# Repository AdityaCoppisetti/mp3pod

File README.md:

for the longest time i wanted to build a mp3 player and 
so i decided to build one using hackclub's macondo program which will also provide me funds
to build it. 
i absolutely love e ink display and decided to use that as i was also using it for my kindle project.
this is how my build looks like 

im a sucker for single purpose devices. 
i used to own a mp3 player when i was a little kid and i used to take that little nugget along with me everywhere. 
but then i lost it which was very unfortunate. 
hackclub's macondo program honestly just gave me a reason to make one. 

and i decided to make it also because it would help me improve my schematic , pcb understanding/ making skills 

here are some questions you must be wondering 
1) did i use ai for this project?
   - yes i kind of did use ai. i used it to make sure my wiring was correct by providing chatgpt screenshots and asking for feedback.
2) is there bluetooth?
   - yes the esp32 module im using has inbuilt bluetooth so i can connect my bluetooth headphones.
3) does it have storage?
   - yes ive put a sd card module and i will insert a sd card into it with my songs already loaded.
4) does it have wifi?
   - ayes the esp 32 module im using also has wifi.
5) can you listen to songs that you havent downloaded?
   - yes using wifi , i can build a ui and load all my songs into my home server and listen to music while connected to wifi anywhere i am.
6) what would happen if i run out of storage
   - i can load the songs that i am not able to download onto my home server and listen to it when the device is online.
7) how do you load songs onto it
   - you can load the songs onto the sd card or you could upload it onto the sd card via bluetooth or wifi using the esp32 module. 

ive gotten really good at building pcbs

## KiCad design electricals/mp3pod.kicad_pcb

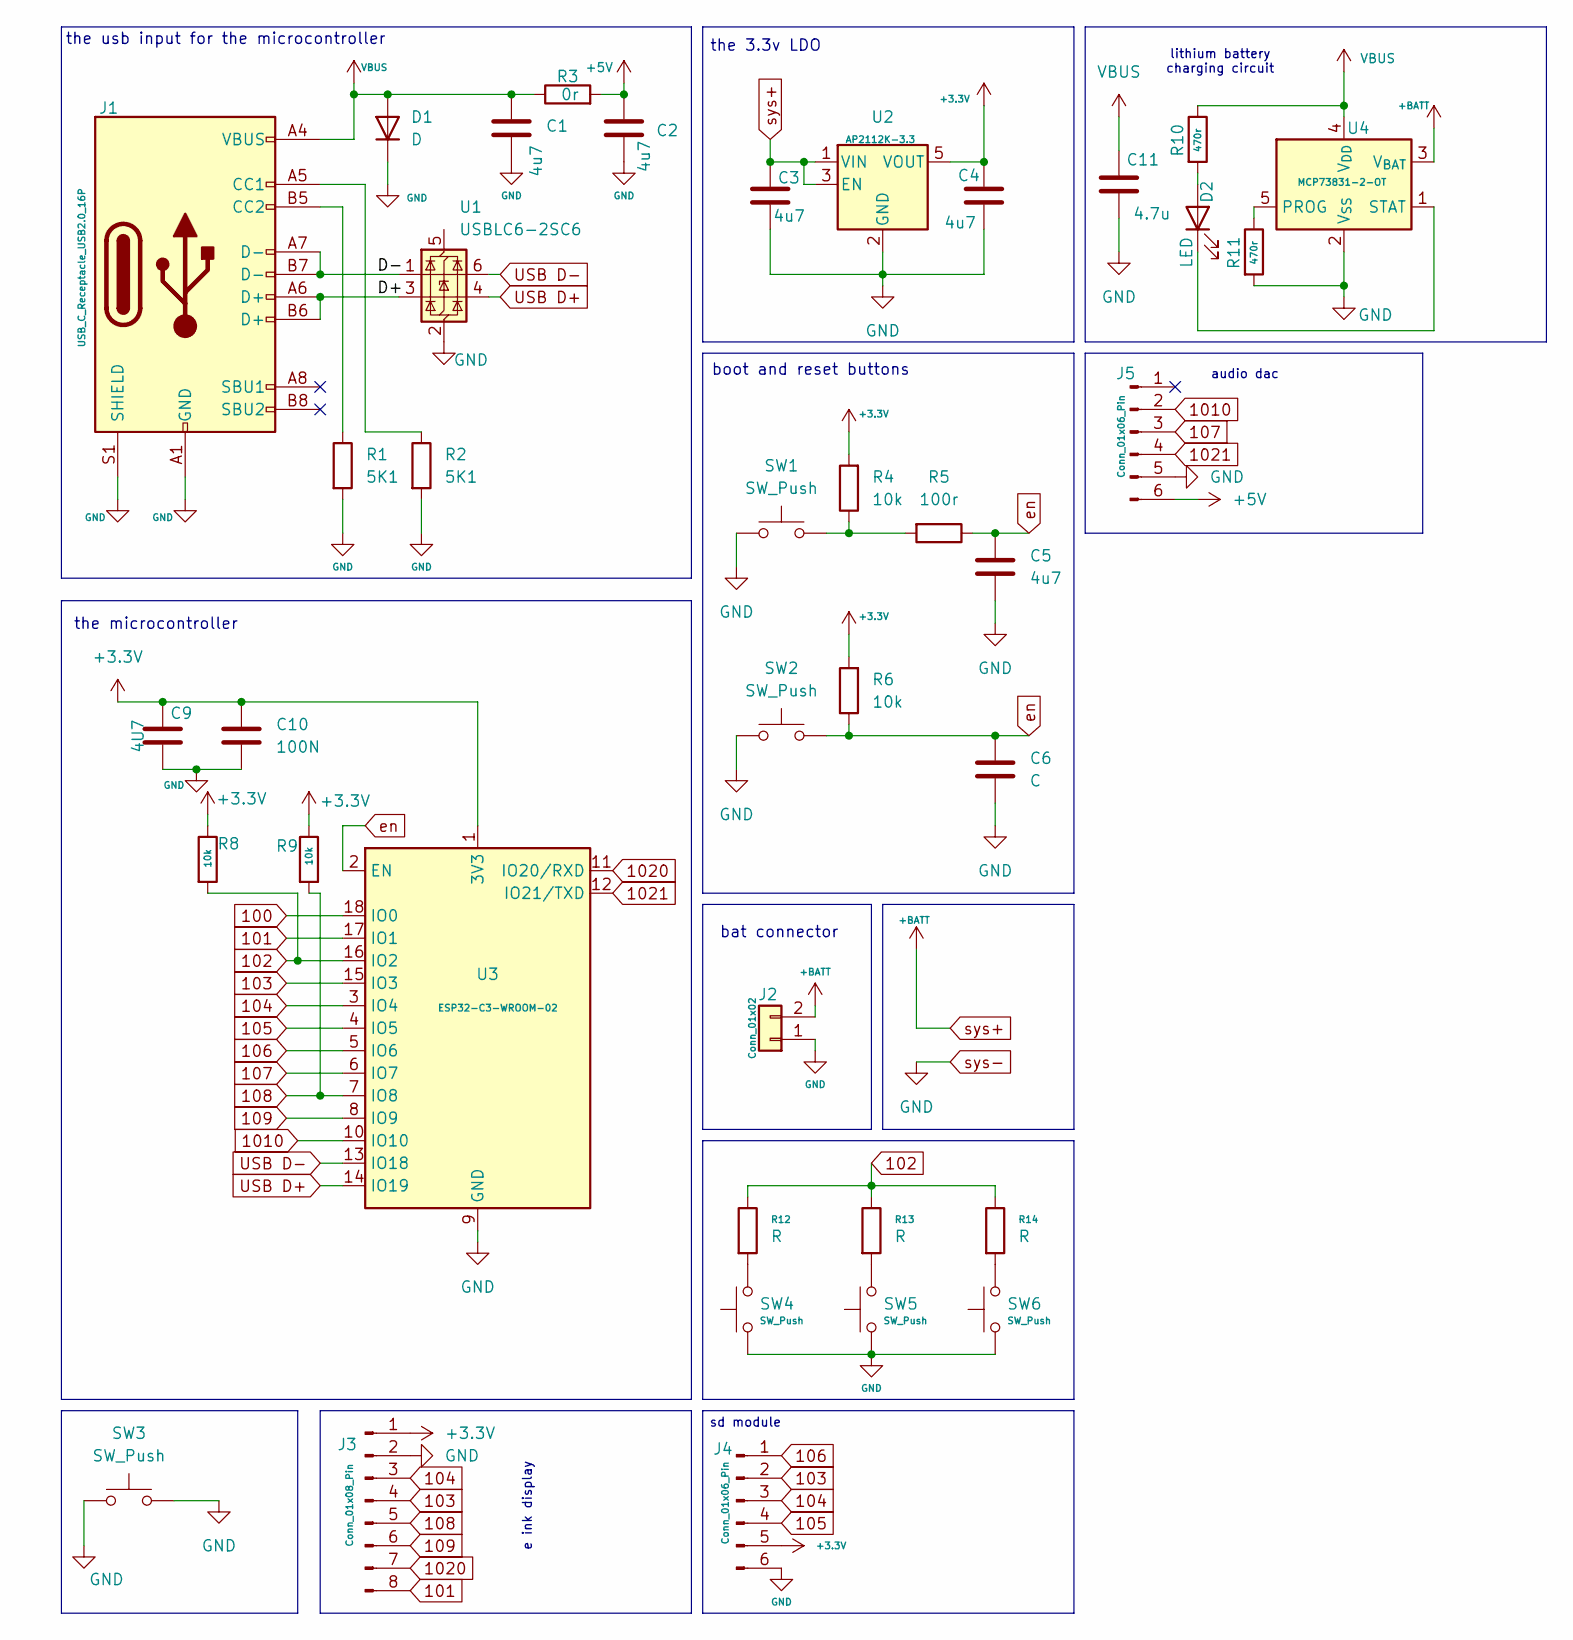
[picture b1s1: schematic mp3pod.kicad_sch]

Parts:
C1, C2, C3, C4, C5: 4u7; C_0805_2012Metric
C6: C; C_0402_1005Metric
C9: 4U7; C_0805_2012Metric
C10: 100N; C_0402_1005Metric
C11: 4.7u; C_0805_2012Metric
D1: D; D_SOD-882D
D2: LED; LED_0402_1005Metric
J1: USB_C_Receptacle_USB2.0_16P; USB_C_Receptacle_G-Switch_GT-USB-7010ASV
J2: Conn_01x02; JST_PH_S2B-PH-K_1x02_P2.00mm_Horizontal
J3: Conn_01x08_Pin; PinHeader_1x08_P2.00mm_Vertical
J4, J5: Conn_01x06_Pin; PinHeader_1x06_P2.00mm_Vertical
R1, R2: 5K1; R_0402_1005Metric
R3: 0r; R_0402_1005Metric
R4, R6, R8, R9: 10k; R_0402_1005Metric
R5: 100r; R_0402_1005Metric
R10: 470r; R_0402_1005Metric
R11: 470r; R_0805_2012Metric
R12, R13, R14: R; PinHeader_1x02_P2.00mm_Vertical
SW1, SW2: SW_Push; SW_SPST_B3U-1000P
SW3, SW4, SW5, SW6: SW_Push; PinHeader_1x02_P2.00mm_Vertical
U1: USBLC6-2SC6; SOT-23-6
U2: AP2112K-3.3; SOT-23-5
U3: ESP32-C3-WROOM-02
U4: MCP73831-2-OT; SOT-23-5

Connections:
100: U3.18 (IO0)
101: J3.8, U3.17 (IO1)
102: R8.2, R12.1, R13.1, R14.1, U3.16 (IO2)
103: J3.4, J4.2, U3.15 (IO3)
104: J3.3, J4.3, U3.3 (IO4)
105: J4.4, U3.4 (IO5)
106: J4.1, U3.5 (IO6)
107: J5.3, U3.6 (IO7)
108: J3.5, R9.2, U3.7 (IO8)
109: J3.6, U3.8 (IO9)
1010: J5.2, U3.10 (IO10)
1020: J3.7, U3.11 (IO20/RXD)
1021: J5.4, U3.12 (IO21/TXD)
+3.3V: C4.1, C9.1, C10.1, J3.1, J4.5, R4.2, R6.2, R8.1, R9.1, U2.5 (VOUT), U3.1 (3V3)
+5V: C2.1, J5.6, R3.2
/D+: J1.A6 (D+), J1.B6 (D+), U1.3 (I/O2)
/D-: J1.A7 (D-), J1.B7 (D-), U1.1 (I/O1)
unnamed 17: D2.2 (A), R10.2; also elsewhere on the board
unnamed 18: D2.1 (K), U4.1 (STAT); also elsewhere on the board
unnamed: J1.A5 (CC1), R2.1
unnamed: J1.B5 (CC2), R1.1
unnamed: R4.1, R5.2, SW1.2
unnamed: R12.2, SW4.2
unnamed: R13.2, SW5.2
unnamed: R14.2, SW6.2
unnamed: R11.1, U4.5 (PROG)
USB D+: U1.4 (I/O2), U3.14 (IO19)
USB D-: U1.6 (I/O1), U3.13 (IO18)
VBUS: C1.1, C11.1, D1.2 (A), J1.A4 (VBUS), J1.A9 (VBUS), J1.B4 (VBUS), J1.B9 (VBUS), R3.1, R10.1, U4.4 (V_{DD})
en: C5.1, C6.1, R5.1, R6.1, SW2.2, U3.2 (EN)
sys+: C3.1, J2.2, U2.1 (VIN), U2.3 (EN), U4.3 (V_{BAT})
sys-: C1.2, C2.2, C3.2, C4.2, C5.2, C6.2, C9.2, C10.2, C11.2, D1.1 (K), J1.A1 (GND), J1.A12 (GND), J1.B1 (GND), J1.B12 (GND), J1.S1 (SHIELD), J2.1, J3.2, J4.6, J5.5, R1.2, R2.2, R11.2, SW1.1, SW2.1, SW3.1, SW3.2, SW4.1, SW5.1, SW6.1, U1.2 (GND), U2.2 (GND), U3.9 (GND), U3.19 (GND), U4.2 (V_{SS})

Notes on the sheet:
bat connector
the 3.3v LDO
audio dac
the usb input for the microcontroller
lithium battery charging circuit
boot and reset buttons
e ink display
sd module
the microcontroller

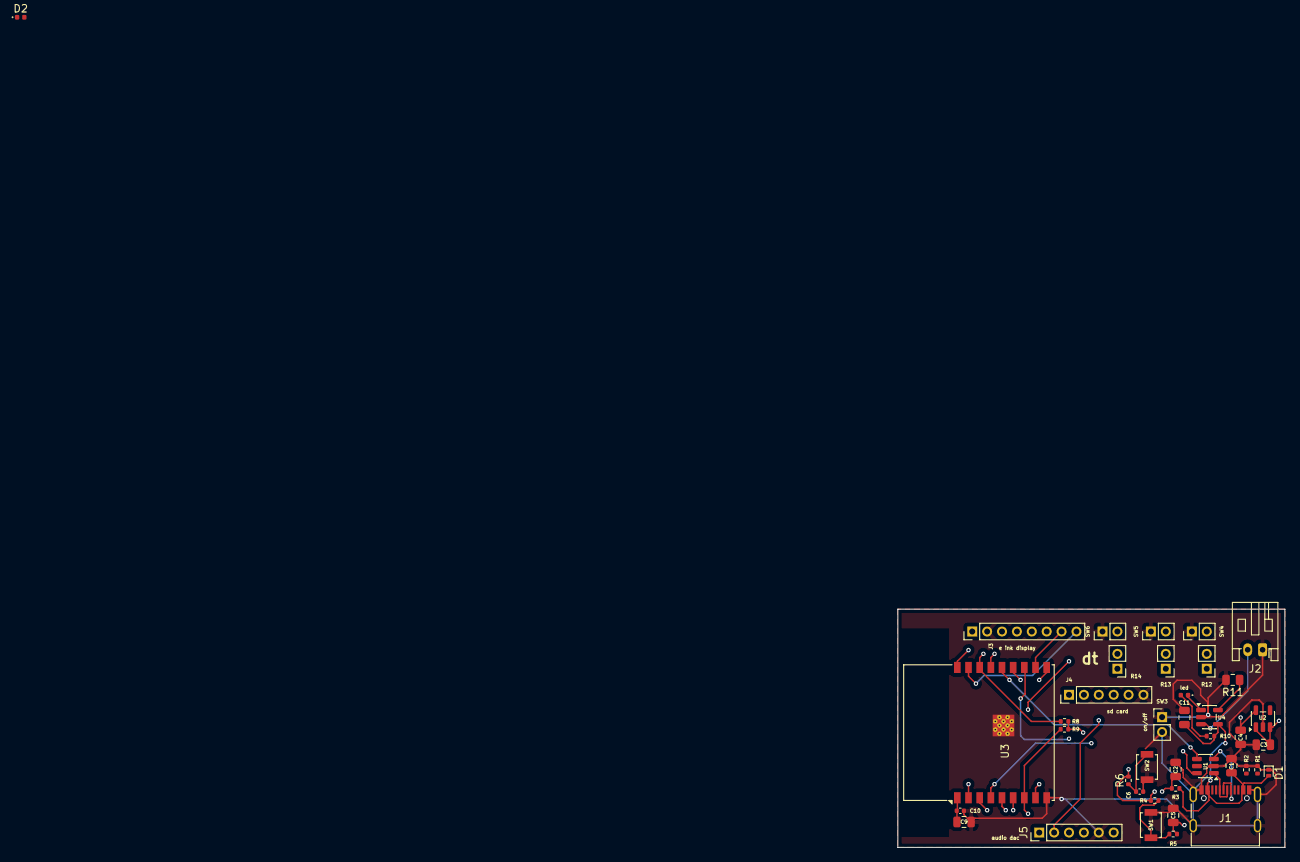
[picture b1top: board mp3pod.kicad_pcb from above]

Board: 4 copper layers, 52.0 x 32.0 mm, 40 parts (0 on the bottom side), 31 nets.

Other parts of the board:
led: LED; LED_0402_1005Metric

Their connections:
unnamed 17: led.2 (A); also elsewhere on the board
unnamed 18: led.1 (K); also elsewhere on the board

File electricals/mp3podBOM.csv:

Reference,KiCad Qty,Value,Footprint,Product,Purchase Qty,Currency,Unit Price,Pack/Line Price,Product Link,in usd
"C1,C2,C3,C4,C5",25,4u7,C_0805_2012Metric,4.7µF 0805 SMD capacitor,10,INR,14,140,https://robu.in/product/mc0805f475z160ct-multicomp-pro-cap-s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,$1.47
C6,1,C,C_0402_1005Metric,4.7µF 0402 SMD capacitor,5,INR,6,30,https://robu.in/product/155r61a475meaad-murata-cap-smd-mlcc-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,$0.31
C9,1,4U7,C_0805_2012Metric,4.7µF 0805 SMD capacitor,10,INR,14,140,https://robu.in/product/mc0805f475z160ct-multicomp-pro-cap-s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,already have
C10,1,100N,C_0402_1005Metric,100nF 0402 SMD capacitor,5,INR,0.55,2.75,https://robu.in/product/0402b104k500nt-fh-50v-100nf-x7r%c2%b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,$0.03
C11,1,4.7u,C_0805_2012Metric,4.7µF 0805 SMD capacitor,10,INR,14,140,https://robu.in/product/mc0805f475z160ct-multicomp-pro-cap-s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,already have
D1,1,D,D_SOD-882D,PMEG3002AELD SOD-882D Schottky diode,5,INR,10,50,https://robu.in/product/pmeg3002aeld315-nexperia-30v-480mv20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,$0.52
D2,1,LED,LED_0402_1005Metric,0402 red SMD LED,5,INR,1.58,7.9,https://robu.in/product/0402-surface-mount-led-red-50pcs/,$0.08
J1,1,USB_C_Receptacle_USB2.0_16P,USB_C_Receptacle_G-Switch_GT-USB-7010ASV,G-Switch GT-USB7010ASV USB-C receptacle,1,USD,0.44,0.44,https://jlcpcb.com/partdetail/GSwitch-GT_USB7010ASV/C2988369,$0.44
J2,1,Conn_01x02,JST_PH_S2B-PH-K_1x02_P2.00mm_Horizontal,JST PH 2-pin 2.00mm horizontal connector,5,USD,0.68,,https://robu.in/product/s2b-ph-klfsn-jst-1x2p-2p-ph-tin-2-25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,$0.68
J3,1,Conn_01x08_Pin,PinHeader_1x08_P2.00mm_Vertical,1x8 2.00mm pitch pin header,10,USD,0.42,4.2,https://robu.in/product/ds1021-09-1x8sf1-a3-0-b6-0-b-connfly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,$0.42
"J4,J5",4,Conn_01x06_Pin,PinHeader_1x06_P2.00mm_Vertical,1x6 2.00mm pitch pin header,10,USD,0.42,,https://robu.in/product/ds1021-09-1x8sf1-a3-0-b6-0-b-connfly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,$0.42
"R1,R2",4,5K1,R_0402_1005Metric,5.1kΩ 0402 SMD resistor,5,USD,0.04,,https://robu.in/product/ac0402fr-075k1l-yageo-res-thick-film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,$0.04
R3,1,0r,R_0402_1005Metric,0Ω 0402 SMD resistor,5,USD,0.013,,https://robu.in/product/erj2ge0r00x-panasonic-100mw-thick-fi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,$0.01
"R4,R6,R8,R9",16,10k,R_0402_1005Metric,10kΩ 0402 SMD resistor,10,USD,0.082,,https://robu.in/product/10k-resistor-smdr-0402-pack-of-50/,$0.08
R5,1,100r,R_0402_1005Metric,100Ω 0402 SMD resistor,2,,,,https://robu.in/product/1-month-warranty-1125/,$0.03
R10,1,470r,R_0402_1005Metric,470Ω 0402 SMD resistor,3,USD,0.0068,,https://robu.in/product/ac0402fr-07470rl-yageo-res-thick-fil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,$0.01
R11,1,470r,R_0805_2012Metric,470Ω 0805 SMD resistor,4,USD,0.042,,https://robu.in/product/rc0805fr-07470rl-yageo-res-thick-fil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,$0.04
"R12,R13,R14",9,R,PinHeader_1x02_P2.00mm_Vertical,1x2 2.00mm pitch pin header,5,USD,0.42,,https://robu.in/product/ds1021-09-1x8sf1-a3-0-b6-0-b-connfly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,$0.42
"SW1,SW2",4,SW_Push,SW_SPST_B3U-1000P,Omron B3U-1000P SMD tactile switch,6,USD,3.99,3.99,https://robu.in/product/b3u-1000p-omron-2-5mm-1-6mm-round-bu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,$3.99
"SW3,SW4,SW5,SW6",16,SW_Push,PinHeader_1x02_P2.00mm_Vertical,1x2 2.00mm connector/header,7,USD,0.23,,https://robu.in/product/aa07a09010000006a-bzcn-3a-125v-3a-25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,$0.23
U1,1,USBLC6-2SC6,SOT-23-6,USBLC6-2SC6,8,USD,0.47,,https://robu.in/product/usblc6-2sc6-ms-msksemi-4-5a-15v-150w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,$0.47
U2,1,AP2112K-3.3,SOT-23-5,AP2112K-3.3,9,USD,0.94,,https://robu.in/product/ap2128k-3-3trg1-diodes-incorporated-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,$0.95
U3,1,ESP32-C3-WROOM-02,ESP32-C3-WROOM-02,ESP32-C3-WROOM-02,10,USD,8.15,,https://robu.in/product/espressif-esp32-c3-wroom-02-n4-module/,$8.15
U4,1,MCP73831-2-OT,SOT-23-5,MCP73831-2-OT,11,USD,5.35,,https://robu.in/product/mcp73831t-2aci-ot-microchip-battery-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,$5.35
BAT1 (external),,Lithium battery,,SP Rechargeable battery (Amazon listing),12,USD,3.13,,https://www.amazon.in/SP-Rechargeable-Connector-Bluetooth-El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,$3.13
pcb from jlcpcb,,pcb,,pcb,1,USD,2,2,,$2.00
shipping for pcb ,,pcb,,pcb,,,30,30,,$28.00
e ink display,1,e ink display,none, e ink display ,1,USD,13.35,13.35,https://robu.in/product/2-13inch-e-ink-paper-display-hat-for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,                                                                                           $13.35
,,,,,,,,,,The total is $70.62 USD.
